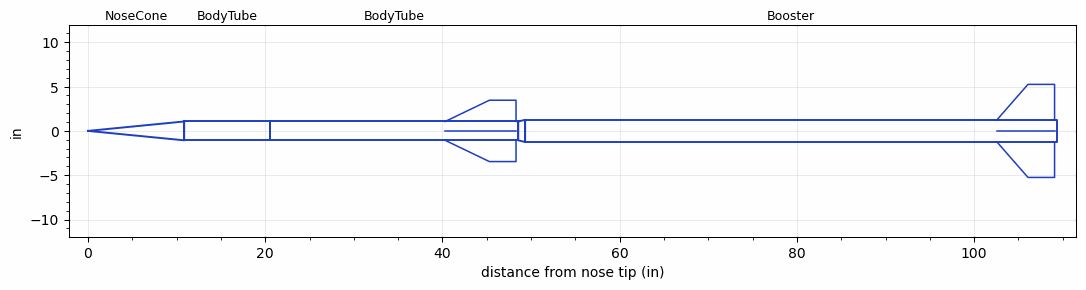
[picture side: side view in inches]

<RASAeroDocument>
 <FileVersion>2</FileVersion>
 <RocketDesign>
  <NoseCone>
   <Length>10.85</Length>
   <Diameter>2.125</Diameter>
   <Shape>Conical</Shape>
   <BluntRadius>0.0625</BluntRadius>
   <Location>0</Location>
  </NoseCone>
  <BodyTube>
   <Length>9.7</Length>
   <Diameter>2.125</Diameter>
   <Location>10.85</Location>
   <Protuberance>
    <StreamlinedNoBaseDrag>0</StreamlinedNoBaseDrag>
    <StreamlinedWithBaseDrag>0.234</StreamlinedWithBaseDrag>
    <InclinedPlate1Angle>0</InclinedPlate1Angle>
    <InclinedPlate1FrontalArea>0</InclinedPlate1FrontalArea>
    <InclinedPlate2Angle>0</InclinedPlate2Angle>
    <InclinedPlate2FrontalArea>0</InclinedPlate2FrontalArea>
   </Protuberance>
  </BodyTube>
  <BodyTube>
   <Length>28</Length>
   <Diameter>2.125</Diameter>
   <Location>20.55</Location>
   <Fin>
    <Count>4</Count>
    <Chord>8</Chord>
    <Span>2.4</Span>
    <SweepDistance>5</SweepDistance>
    <TipChord>3</TipChord>
    <Thickness>0.13</Thickness>
    <LERadius>0.01</LERadius>
    <Location>8.25</Location>
    <AirfoilSection>Hexagonal</AirfoilSection>
    <FX1>0.75</FX1>
    <FX3>0.75</FX3>
   </Fin>
  </BodyTube>
  <Booster>
   <Length>60</Length>
   <Diameter>2.5</Diameter>
   <InsideDiameter>2.125</InsideDiameter>
   <RailGuideDiameter>0.625</RailGuideDiameter>
   <RailGuideHeight>0.4</RailGuideHeight>
   <Location>48.55</Location>
   <ShoulderLength>0.775</ShoulderLength>
   <Fin>
    <Count>4</Count>
    <Chord>6.5</Chord>
    <Span>4</Span>
    <SweepDistance>3.5</SweepDistance>
    <TipChord>3</TipChord>
    <Thickness>0.375</Thickness>
    <LERadius>0.01</LERadius>
    <Location>6.75</Location>
    <AirfoilSection>Hexagonal</AirfoilSection>
    <FX1>0.5</FX1>
    <FX3>0.5</FX3>
   </Fin>
  </Booster>
  <Surface>Camouflage Paint</Surface>
  <ModifiedBarrowman>True</ModifiedBarrowman>
  <Turbulence>True</Turbulence>
  <UseBooster1>False</UseBooster1>
  <UseBooster2>False</UseBooster2>
 </RocketDesign>
 <LaunchSite>
  <Altitude>2000</Altitude>
  <Pressure>0</Pressure>
  <RodAngle>2</RodAngle>
  <RodLength>20</RodLength>
  <Temperature>85</Temperature>
  <WindSpeed>7</WindSpeed>
 </LaunchSite>
 <Recovery>
  <Altitude1>1000</Altitude1>
  <Altitude2>1000</Altitude2>
  <DeviceType1>None</DeviceType1>
  <DeviceType2>None</DeviceType2>
  <Event1>False</Event1>
  <Event2>False</Event2>
  <Size1>1</Size1>
  <Size2>1</Size2>
  <EventType1>None</EventType1>
  <EventType2>None</EventType2>
  <CD1>1.33</CD1>
  <CD2>1.33</CD2>
 </Recovery>
 <SimulationList>
  <Simulation>
   <SustainerEngine>L1719  (TsKrush)</SustainerEngine>
   <SustainerLaunchWt>8</SustainerLaunchWt>
   <SustainerNozzleDiameter>1.9</SustainerNozzleDiameter>
   <SustainerCG>28</SustainerCG>
   <SustainerIgnitionDelay>12</SustainerIgnitionDelay>
   <Booster1Engine>M2500  (Chase)</Booster1Engine>
   <Booster1LaunchWt>26.2</Booster1LaunchWt>
   <Booster1SeparationDelay>0</Booster1SeparationDelay>
   <Booster1IgnitionDelay>0</Booster1IgnitionDelay>
   <Booster1CG>70</Booster1CG>
   <Booster1NozzleDiameter>2</Booster1NozzleDiameter>
   <IncludeBooster1>True</IncludeBooster1>
   <Booster2Delay>0</Booster2Delay>
   <IncludeBooster2>False</IncludeBooster2>
   <TimetoApogee>91.72042</TimetoApogee>
   <MaxAltitude>127561.7</MaxAltitude>
   <MaxVelocity>5074.705</MaxVelocity>
  </Simulation>
  <Simulation>
   <SustainerEngine>L2342  (BPS)</SustainerEngine>
   <SustainerLaunchWt>10</SustainerLaunchWt>
   <SustainerCG>36</SustainerCG>
   <SustainerIgnitionDelay>2</SustainerIgnitionDelay>
   <Booster1Engine>M2380  (AeroTech)</Booster1Engine>
   <Booster1LaunchWt>27</Booster1LaunchWt>
   <Booster1SeparationDelay>0</Booster1SeparationDelay>
   <Booster1IgnitionDelay>0</Booster1IgnitionDelay>
   <Booster1CG>70</Booster1CG>
   <IncludeBooster1>True</IncludeBooster1>
   <Booster2Delay>0</Booster2Delay>
   <IncludeBooster2>False</IncludeBooster2>
   <TimetoApogee>93.79086</TimetoApogee>
   <MaxAltitude>132390.8</MaxAltitude>
   <MaxVelocity>5086.274</MaxVelocity>
  </Simulation>
  <Simulation>
   <SustainerEngine>L1719  (TsKrush)</SustainerEngine>
   <SustainerLaunchWt>8</SustainerLaunchWt>
   <SustainerNozzleDiameter>1.9</SustainerNozzleDiameter>
   <SustainerCG>28</SustainerCG>
   <SustainerIgnitionDelay>0</SustainerIgnitionDelay>
   <Booster1SeparationDelay>0</Booster1SeparationDelay>
   <Booster1IgnitionDelay>0</Booster1IgnitionDelay>
   <IncludeBooster1>False</IncludeBooster1>
   <Booster2Delay>0</Booster2Delay>
   <IncludeBooster2>False</IncludeBooster2>
   <TimetoApogee>34.31025</TimetoApogee>
   <MaxAltitude>31581.86</MaxAltitude>
   <MaxVelocity>4102.84</MaxVelocity>
  </Simulation>
 </SimulationList>
</RASAeroDocument>
